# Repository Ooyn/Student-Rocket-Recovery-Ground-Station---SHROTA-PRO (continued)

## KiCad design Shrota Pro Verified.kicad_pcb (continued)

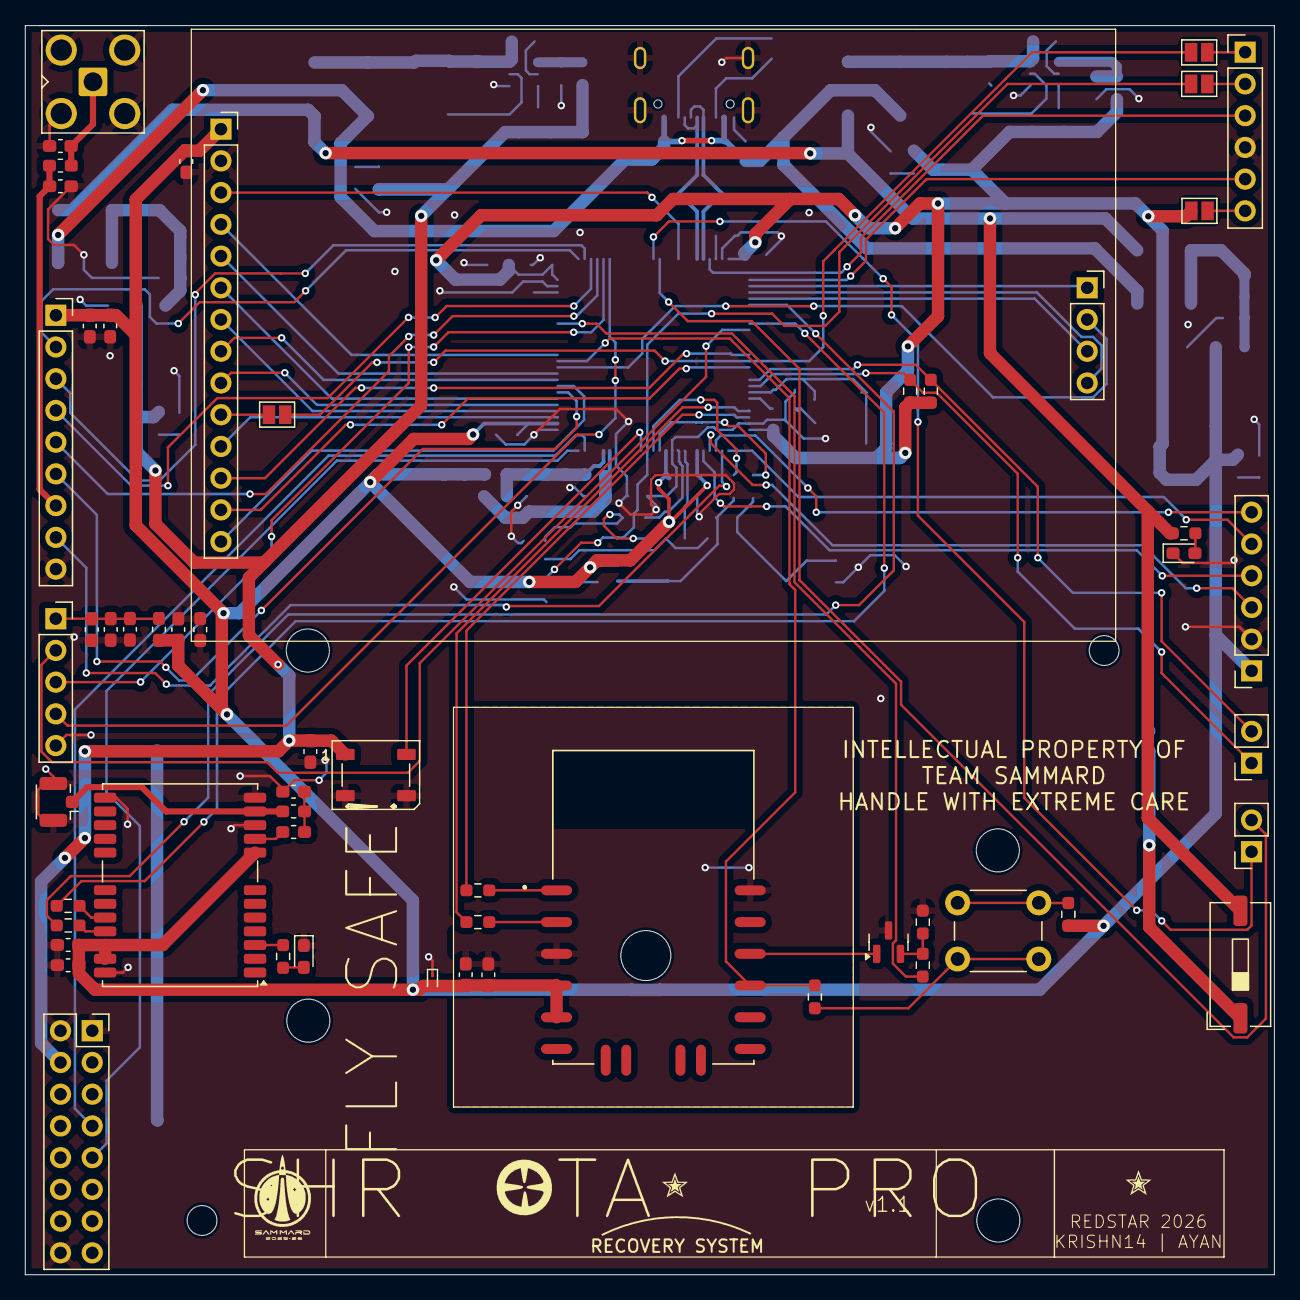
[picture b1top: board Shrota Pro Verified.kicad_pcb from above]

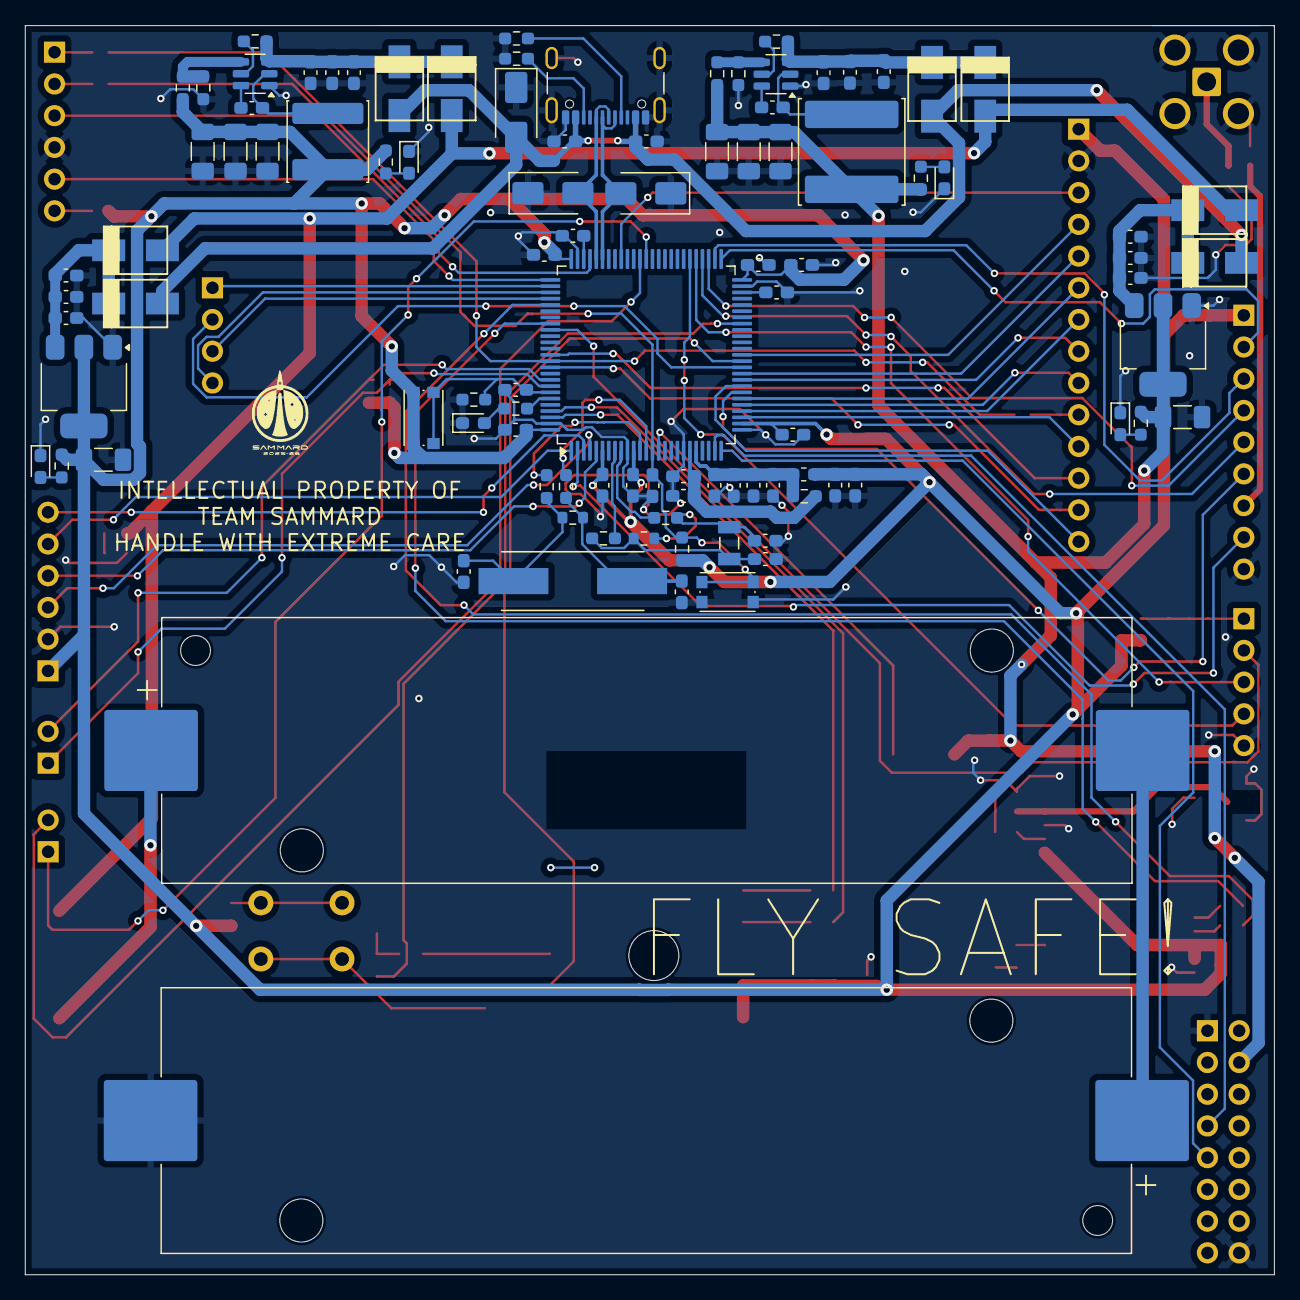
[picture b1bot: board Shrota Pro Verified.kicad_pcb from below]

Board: 2 copper layers, 100.0 x 100.0 mm, 156 parts (100 on the bottom side), 109 nets.

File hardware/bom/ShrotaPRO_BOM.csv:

Designators,Qty,Value / Part,KiCad Symbol,Footprint / Package
BT1,1,7.4_1,Device:Battery_Cell,BatteryHolder_Keystone_1042_1x18650
BT3,1,7.4_2,Device:Battery_Cell,BatteryHolder_Keystone_1042_1x18650
"C1, C4, C7, C50, C51",5,10uF,Device:C,C_0603_1608Metric_Pad1.08x0.95mm_HandSolder
"C2, C6, C16, C19, C20, C23, C28, C29, C35, C37, C42",11,10u,Device:C,C_0603_1608Metric_Pad1.08x0.95mm_HandSolder
"C3, C39",2,22u,Device:C,C_1206_3216Metric_Pad1.33x1.80mm_HandSolder
"C5, C38, C44, C80",4,1u,Device:C,C_0603_1608Metric_Pad1.08x0.95mm_HandSolder
"C8, C9, C52, C54",4,0.1uF,Device:C,C_0603_1608Metric_Pad1.08x0.95mm_HandSolder
"C10, C12, C13, C14, C25, C26, C27, C30, C31, C32, C43, C45, C53, C55, C61",15,100n,Device:C,C_0603_1608Metric_Pad1.08x0.95mm_HandSolder
"C11, C56, C57, C58, C59, C60",6,22uF,Device:C,C_1206_3216Metric_Pad1.33x1.80mm_HandSolder
C15,1,100nF,Device:C,C_0603_1608Metric_Pad1.08x0.95mm_HandSolder
"C17, C18",2,20p,Device:C,C_0603_1608Metric_Pad1.08x0.95mm_HandSolder
"C21, C72",2,0.1u,Device:C,C_0603_1608Metric_Pad1.08x0.95mm_HandSolder
C22,1,47p,Device:C,C_0603_1608Metric_Pad1.08x0.95mm_HandSolder
C24,1,100 nF,Device:C,C_0603_1608Metric_Pad1.08x0.95mm_HandSolder
C36,1,22 uF,Device:C,C_0603_1608Metric_Pad1.08x0.95mm_HandSolder
"C40, C41",2,2.2u,Device:C,C_0603_1608Metric_Pad1.08x0.95mm_HandSolder
"C48, C49",2,10p,Device:C,C_0603_1608Metric_Pad1.08x0.95mm_HandSolder
C73,1,10n,Device:C,C_0603_1608Metric_Pad1.08x0.95mm_HandSolder
"C81, C82",2,6.5p,Device:C,C_0603_1608Metric_Pad1.08x0.95mm_HandSolder
D1,1,ESD9L5.0ST5G,Diode:ESD9B5.0ST5G,D_SOD-923
"D2, D7, D8, D9, D10, D11, D23",7,LED,Device:LED,LED_0603_1608Metric_Pad1.05x0.95mm_HandSolder
"D3, D5, D6",3,SMAJ7.5CA,Diode:SMAJ7.5CA,D_SMA
"D18, D19, D20, D21, D22, D25, D26, D27",8,SS14,Diode:SS14,DO-214AC
D24,1,WS2812B,LED:WS2812B,LED_WS2812B_PLCC4_5.0x5.0mm_P3.2mm
"FB1, FB3, FB5",3,120R,Device:FerriteBead,L_0603_1608Metric_Pad1.05x0.95mm_HandSolder
FB4,1,1KR,Device:FerriteBead,L_0603_1608Metric_Pad1.05x0.95mm_HandSolder
J1,1,Conn_01x06_Pin,Connector:Conn_01x06_Pin,PinHeader_1x06_P2.54mm_Vertical
J2,1,LoRaRYLR998,Connector:Conn_01x05_Socket,PinSocket_1x05_P2.54mm_Vertical
J3,1,USB_C_Receptacle_USB2.0_14P,Connector:USB_C_Receptacle_USB2.0_14P,USB_C_Receptacle_GCT_USB4105-xx-A_16P_TopMnt_Horizontal
J4,1,Conn_01x04_Pin,Connector:Conn_01x04_Pin,PinSocket_1x04_P2.54mm_Vertical
J5,1,Conn_01x14_Pin,Connector:Conn_01x14_Pin,PinSocket_1x14_P2.54mm_Vertical
"J8, J9",2,Conn_01x02_Pin,Connector:Conn_01x02_Pin,PinSocket_1x02_P2.54mm_Vertical
J10,1,Conn_Coaxial_Small,Connector:Conn_Coaxial_Small,SMA_Amphenol_901-143_Horizontal
J11,1,Conn_Coaxial,Connector:Conn_Coaxial,U.FL_Hirose_U.FL-R-SMT-1_Vertical
J14,1,Conn_01x16_Socket,Connector:Conn_01x16_Socket,PinSocket_2x08_P2.54mm_Vertical
J15,1,Conn_01x06_Socket,Connector:Conn_01x06_Socket,PinSocket_1x06_P2.54mm_Vertical
J80,1,Conn_01x09_Pin,Connector:Conn_01x09_Pin,PinSocket_1x09_P2.54mm_Vertical
L1,1,2.2u,Device:L,L_Sunlord_SWPA6045S
L2,1,3.3u,Device:L,L_Sunlord_SWPA8040S
L5,1,27n,Device:L,L_0603_1608Metric_Pad1.05x0.95mm_HandSolder
L35,1,7.5n,Device:L,L_0603_1608Metric_Pad1.05x0.95mm_HandSolder
"R1, R5, R11, R33, R34, R36, R37, R39",8,0,Device:R,R_0603_1608Metric_Pad0.98x0.95mm_HandSolder
"R2, R9, R10, R12, R14, R16, R19",7,10k,Device:R,R_0603_1608Metric_Pad0.98x0.95mm_HandSolder
"R3, R17",2,27,Device:R,R_0603_1608Metric_Pad0.98x0.95mm_HandSolder
"R4, R8, R21",3,4.7k,Device:R,R_0603_1608Metric_Pad0.98x0.95mm_HandSolder
"R6, R7",2,5.1k,Device:R,R_0603_1608Metric_Pad0.98x0.95mm_HandSolder
R13,1,33.2k,Device:R,R_0603_1608Metric_Pad0.98x0.95mm_HandSolder
"R15, R25, R26, R27, R29",5,1k,Device:R,R_0603_1608Metric_Pad0.98x0.95mm_HandSolder
R18,1,54.9k,Device:R,R_0603_1608Metric_Pad0.98x0.95mm_HandSolder
R20,1,1K,Device:R,R_0603_1608Metric_Pad0.98x0.95mm_HandSolder
R22,1,47k,Device:R,R_0603_1608Metric_Pad0.98x0.95mm_HandSolder
R32,1,150,Device:R,R_0603_1608Metric_Pad0.98x0.95mm_HandSolder
"R35, R38",2,10M,Device:R,R_0603_1608Metric
SW1,1,SW_Push,Switch:SW_Push,SW_PUSH_6mm
"SW5, SW7",2,SW_Push,Switch:SW_Push,SW_Push_1P1T_NO_CK_KMR2
SW6,1,SW_SPST,Switch:SW_SPST,SW_DIP_SPSTx01_Slide_9.78x4.72mm_W8.61mm_P2.54mm
"TPS_3.3V1, TPS_5V1",2,TPS563200,Regulator_Switching:TPS563200,SOT-23-6
U1,1,L89,L89:L89,XCVR_L89
U2,1,AMS1117-5.0,Regulator_Linear:AMS1117-5.0,SOT-223-3_TabPin2
U3,1,AMS1117-3.3,Regulator_Linear:AMS1117-3.3,SOT-223-3_TabPin2
U7,1,STM32H743VITx,MCU_ST_STM32H7:STM32H743VITx,LQFP-100_14x14mm_P0.5mm
U9,1,NEO-M8N,RF_GPS:NEO-M8N,ublox_NEO
Y4,1,32.768KHz,Device:Crystal,XTAL_ABS07AIG-32.768KHZ-1-T
Y5,1,25MHz,Device:Crystal,XTAL_ABLS-25.000MHZ-B2F-T

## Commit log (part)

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2026-03-11 Create LICENSE
